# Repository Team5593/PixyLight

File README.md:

# PixyLight
Programmable LED ring for the Pixy Camera

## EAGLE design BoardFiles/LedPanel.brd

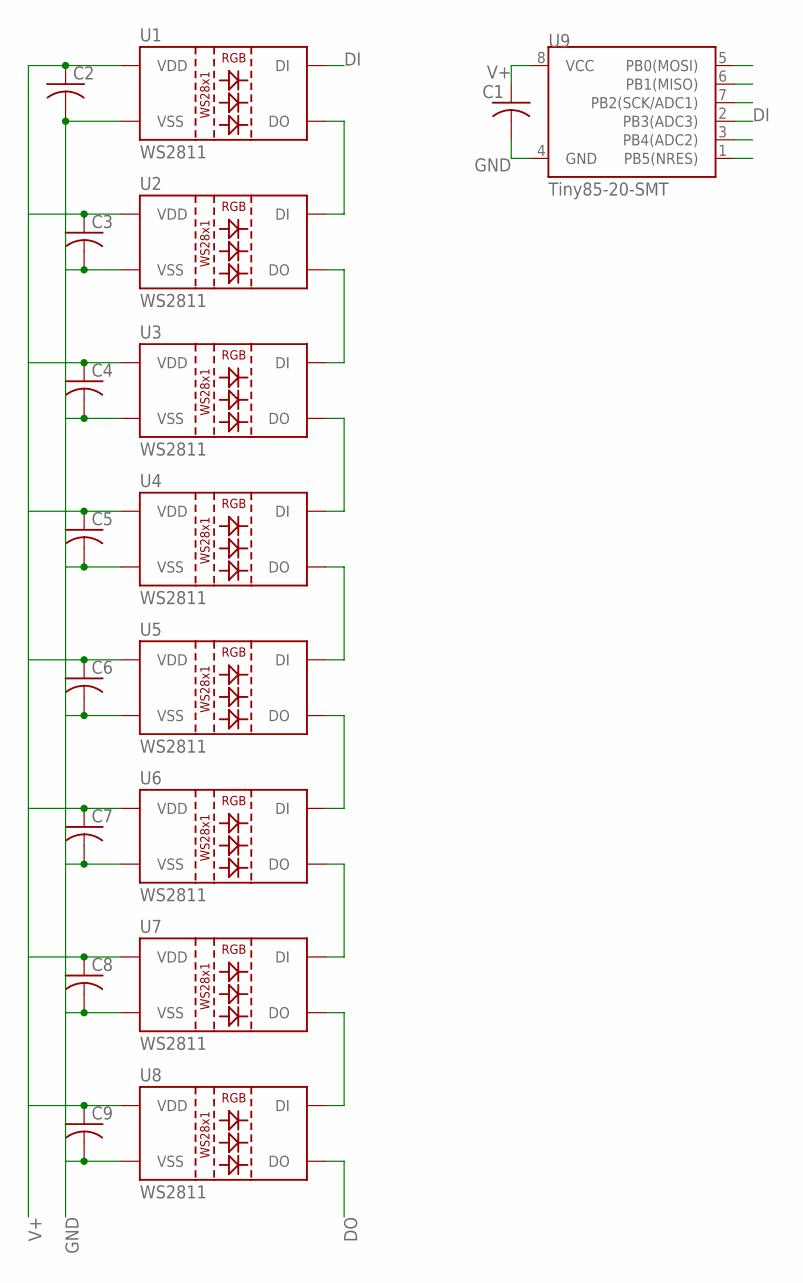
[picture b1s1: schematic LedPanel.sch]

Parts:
C1, C2, C3, C4, C5, C6, C7, C8, C9: C-USC0805; C0805
U1, U2, U3, U4, U5, U6, U7, U8: WS2811; LED-TRICOLOR-5050-IC
U9: Tiny85-20-SMT; SO08-EIAJ

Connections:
DI: U1.2 (DI), U9.2 (PB3(ADC3))
DO: U8.1 (DO)
GND: C1.2, C2.2, C3.2, C4.2, C5.2, C6.2, C7.2, C8.2, C9.2, U1.6 (VSS), U2.6 (VSS), U3.6 (VSS), U4.6 (VSS), U5.6 (VSS), U6.6 (VSS), U7.6 (VSS), U8.6 (VSS), U9.4 (GND)
unnamed: U1.1 (DO), U2.2 (DI)
unnamed: U2.1 (DO), U3.2 (DI)
unnamed: U3.1 (DO), U4.2 (DI)
unnamed: U4.1 (DO), U5.2 (DI)
unnamed: U5.1 (DO), U6.2 (DI)
unnamed: U6.1 (DO), U7.2 (DI)
unnamed: U7.1 (DO), U8.2 (DI)
V+: C1.1, C2.1, C3.1, C4.1, C5.1, C6.1, C7.1, C8.1, C9.1, U1.3 (VDD), U1.5 (VDD), U2.3 (VDD), U2.5 (VDD), U3.3 (VDD), U3.5 (VDD), U4.3 (VDD), U4.5 (VDD), U5.3 (VDD), U5.5 (VDD), U6.3 (VDD), U6.5 (VDD), U7.3 (VDD), U7.5 (VDD), U8.3 (VDD), U8.5 (VDD), U9.8 (VCC)

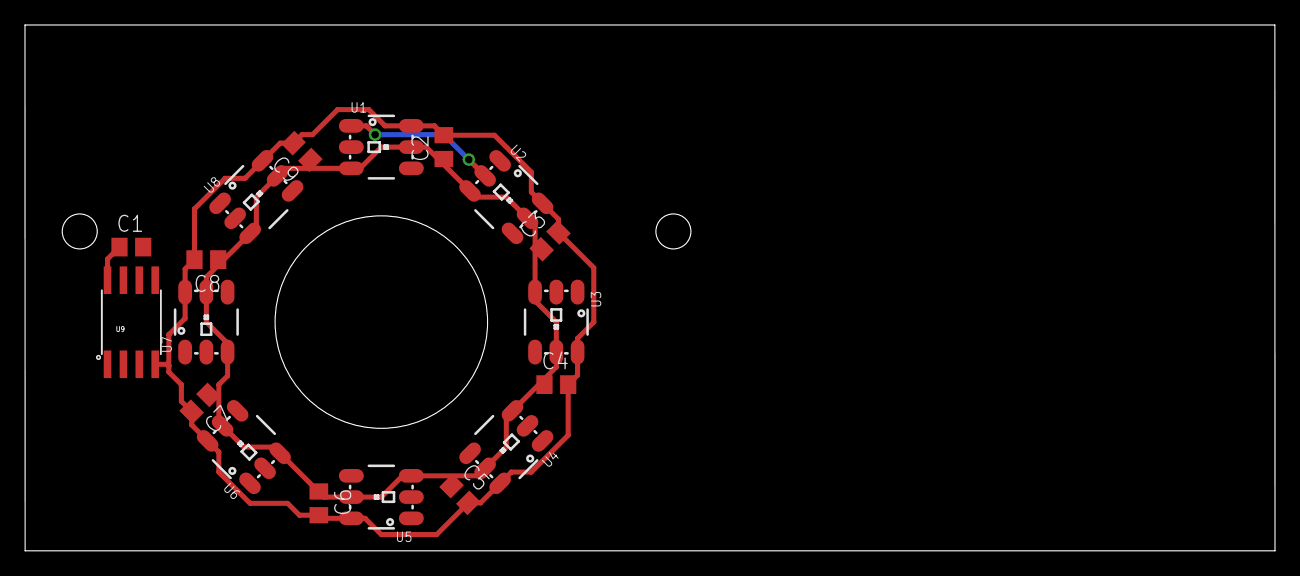
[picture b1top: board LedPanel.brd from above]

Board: 2 copper layers, 100.0 x 42.1 mm, 18 parts (0 on the bottom side), 10 nets.

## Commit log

2017-03-29 some stuff

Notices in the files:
parts and their libraries:
SparkFun-LED: Licensing: Creative Commons ShareAlike 4.0 International - https://creativecommons.org/licenses/by-sa/4.0
